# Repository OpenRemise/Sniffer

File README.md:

# Sniffer

<a href="https://openremise.at">
<picture>
  <source media="(prefers-color-scheme: dark)" srcset="https://github.com/OpenRemise/.github/raw/master/data/icons/icon_dark.svg">
  
</picture>
</a>

The Sniffer is a small add-on board that turns a [Raspberry Pi Pico](https://www.raspberrypi.com/products/raspberry-pi-pico) into a [DCC](https://en.wikipedia.org/wiki/Digital_Command_Control) (and BiDi) logic analyzer.

### Features
- **Requires** [Raspberry Pi Pico](https://www.raspberrypi.com/products/raspberry-pi-pico) (or [Pico 2](https://www.raspberrypi.com/products/raspberry-pi-pico-2))
- No external supply
- ≥12V track voltage
- 3.3V logic level outputs for
  - P track
  - N track
  - BiDi
  - BiDi polarity
- Opto-isolation
- Supported software
  - [PulseView](https://github.com/sigrokproject/pulseview)
  - [LogicAnalyzer](https://github.com/gusmanb/logicanalyzer)

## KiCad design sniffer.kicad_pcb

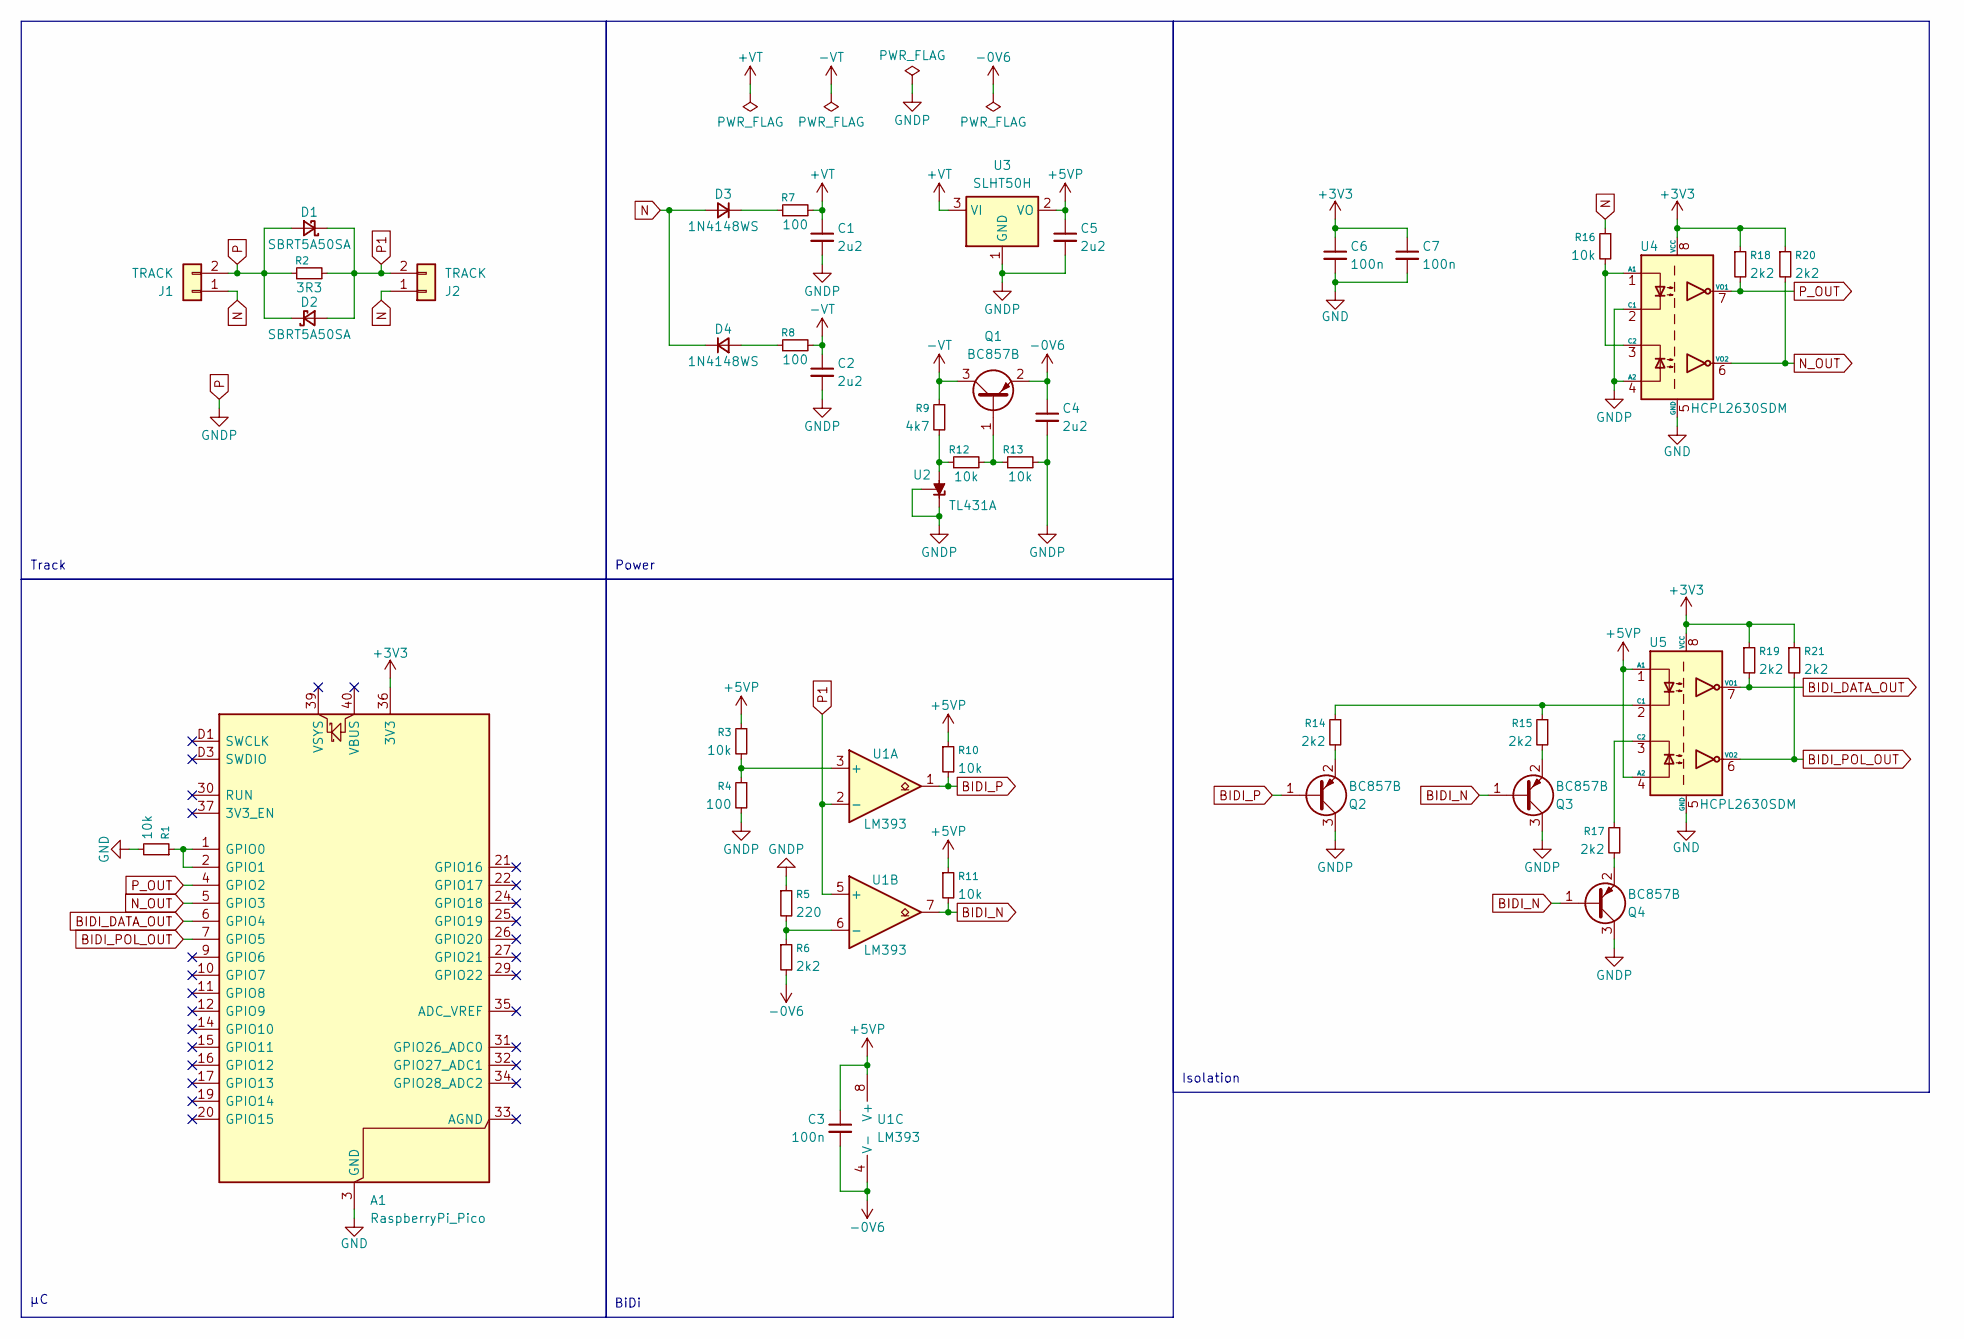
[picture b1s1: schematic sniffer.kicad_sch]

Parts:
A1: RaspberryPi_Pico; RaspberryPi_Pico_SMD_HandSolder
C1, C2, C4, C5: 2u2; C_1206_3216Metric_Pad1.33x1.80mm_HandSolder
C3, C6, C7: 100n; C_0805_2012Metric_Pad1.18x1.45mm_HandSolder
D1, D2: SBRT5A50SA; D_SMA_Handsoldering
D3, D4: 1N4148WS; D_SOD-323_HandSoldering
J1, J2: TRACK; PhoenixContact_MC_1,5_2-G-3.5_1x02_P3.50mm_Horizontal
Q1, Q2, Q3, Q4: BC857B; SOT-23_Handsoldering
R1, R3, R10, R11, R12, R13, R16: 10k; R_0805_2012Metric_Pad1.20x1.40mm_HandSolder
R2: 3R3; R_0805_2012Metric_Pad1.20x1.40mm_HandSolder
R4, R7, R8: 100; R_0805_2012Metric_Pad1.20x1.40mm_HandSolder
R5: 220; R_0805_2012Metric_Pad1.20x1.40mm_HandSolder
R6, R14, R15, R17, R18, R19, R20, R21: 2k2; R_0805_2012Metric_Pad1.20x1.40mm_HandSolder
R9: 4k7; R_0805_2012Metric_Pad1.20x1.40mm_HandSolder
U1: LM393; SOIC-8_3.9x4.9mm_P1.27mm
U2: TL431A; SOT-23_Handsoldering
U3: SLHT50H; SOT-23_Handsoldering
U4, U5: HCPL2630SDM; SMDIP-8_W9.53mm

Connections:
+3V3: A1.36 (3V3), C6.1, C7.1, R18.1, R19.1, R20.1, R21.1, U4.8 (VCC), U5.8 (VCC)
+5VP: C3.1, C5.1, R3.1, R10.1, R11.1, U1.8 (V+), U3.2 (VO), U5.1 (A1), U5.4 (A2)
+VT: C1.1, R7.2, U3.3 (VI)
-0V6: C3.2, C4.1, Q1.2 (E), R6.2, U1.4 (V-)
-VT: C2.1, Q1.3 (C), R8.2, R9.1
BIDI_DATA_OUT: A1.6 (GPIO4), R19.2, U5.7 (VO1)
BIDI_N: Q3.1 (B), Q4.1 (B), R11.2, U1.7
BIDI_P: Q2.1 (B), R10.2, U1.1
BIDI_POL_OUT: A1.7 (GPIO5), R21.2, U5.6 (VO2)
GND: A1.3 (GND), A1.8 (GND), A1.13 (GND), A1.18 (GND), A1.23 (GND), A1.28 (GND), A1.38 (GND), A1.D2 (GND), C6.2, C7.2, R1.2, U4.5 (GND), U5.5 (GND)
N: D3.2 (A), D4.1 (K), J1.1, J2.1, R16.1
N_OUT: A1.5 (GPIO3), R20.2, U4.6 (VO2)
unnamed: A1.1 (GPIO0), A1.2 (GPIO1), R1.1
unnamed: D3.1 (K), R7.1
unnamed: D4.2 (A), R8.1
unnamed: Q1.1 (B), R12.2, R13.1
unnamed: Q2.2 (E), R14.2
unnamed: Q3.2 (E), R15.2
unnamed: Q4.2 (E), R17.2
unnamed: R3.2, R4.1, U1.3 (+)
unnamed: R5.2, R6.1, U1.6 (-)
unnamed: R9.2, R12.1, U2.3 (A)
unnamed: R16.2, U4.1 (A1), U4.3 (C2)
unnamed: R14.1, R15.1, U5.2 (C1)
unnamed: R17.1, U5.3 (C2)
P: C1.2, C2.2, C4.2, C5.2, D1.2 (A), D2.1 (K), J1.2, Q2.3 (C), Q3.3 (C), Q4.3 (C), R2.1, R4.2, R5.1, R13.2, U2.1 (K), U2.2 (REF), U3.1 (GND), U4.2 (C1), U4.4 (A2)
P1: D1.1 (K), D2.2 (A), J2.2, R2.2, U1.2 (-), U1.5 (+)
P_OUT: A1.4 (GPIO2), R18.2, U4.7 (VO1)

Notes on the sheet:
BiDi
Isolation
Track
Power

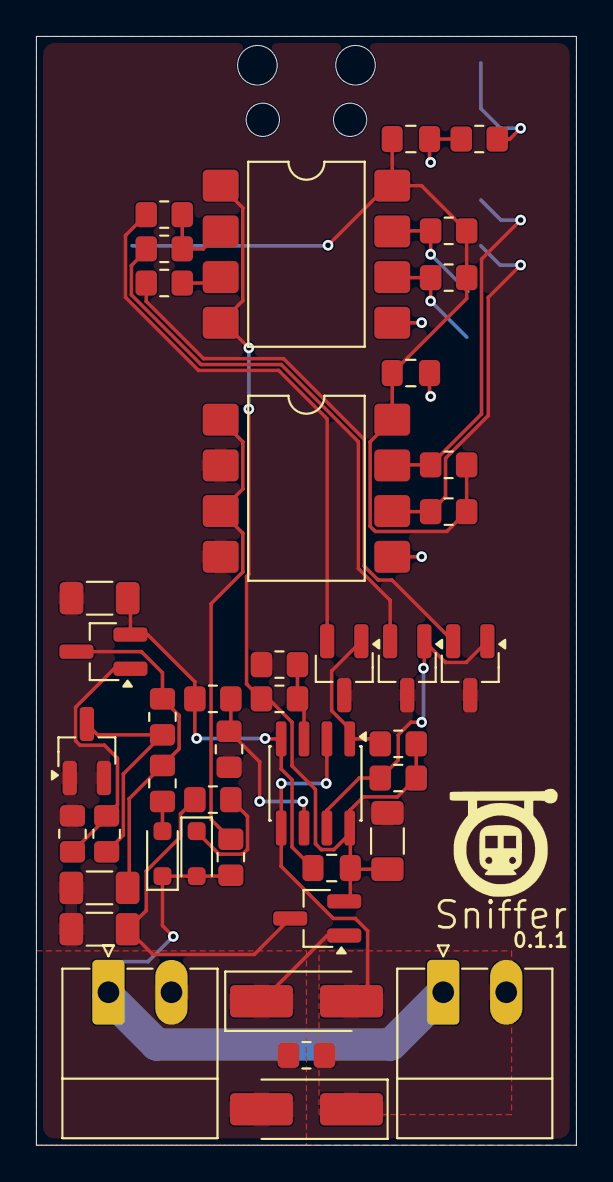
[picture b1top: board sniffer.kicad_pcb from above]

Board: 2 copper layers, 30.0 x 61.6 mm, 44 parts (1 on the bottom side), 28 nets.

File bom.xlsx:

|  |  | S3Main PCS BOM
Item # | *Designator | *Qty | Manufacturer | *Mfg Part # | Description / Value | *Package/Footprint | Type | Your Instructions / Notes
1 | A1 | 1 | Raspberry Pi | SC1631 | RASPBERRY PI PICO 2 RP2350 |  | SMD
2 | C1,C2,C4,C5 | 4 | Samsung Electro-Mechanics | CL31B225KBHNNNE | CAP CER 2.2UF 50V X7R 1206 | 1206 | SMD
3 | C3,C6,C7 | 3 | Samsung Electro-Mechanics | CL21B104KBCNNNC | CAP CER 0.1UF 50V X7R 0805 | 0805 | SMD
4 | D1,D2 | 2 | Diodes Incorporated | SBRT5A50SA-13 | DIODE SBR 50V 5A SMA | SMA | SMD
5 | D3,D4 | 2 | Diodes Incorporated | 1N4148WS-7-F | DIODE STANDARD 75V 150MA SOD323 | SOD-323 | SMD
6 | J1,J2 | 2 | Phoenix Contact | 1844210 | TERM BLOCK HDR 2POS 90DEG 3.5MM |  | THT
7 | Q1,Q2,Q3,Q4 | 4 | Taiwan Semiconductor Corporation | BC857A RFG | TRANS PNP 45V 0.1A SOT-23 | SOT-23-3 | SMD
8 | R1,R3,R10,R11,R12,R13,R16 | 7 | YAGEO | RC0805FR-0710KL | RES 10K OHM 1% 1/8W 0805 | 0805 | SMD
9 | R2 | 1 | Vishay Dale | RCS08053R30FKEA | RES 3.3 OHM 1% 3/4W 0805 | 0805 | SMD
10 | R4,R7,R8 | 3 | YAGEO | RC0805FR-07100RL | RES 100 OHM 1% 1/8W 0805 | 0805 | SMD
11 | R5 | 1 | YAGEO | RC0805FR-07220RL | RES 220 OHM 1% 1/8W 0805 | 0805 | SMD
12 | R6,R14,R15,R17,R18,R19,R20,R21 | 8 | YAGEO | RC0805FR-072K2L | RES 2.2K OHM 1% 1/8W 0805 | 0805 | SMD
13 | R9 | 1 | YAGEO | RC0805FR-074K7L | RES 4.7K OHM 1% 1/8W 0805 | 0805 | SMD
14 | U1 | 1 | onsemi | LM393DR2G | IC COMPARATOR 2 GEN PUR 8SOIC | SOIC-8 | SMD
15 | U2 | 1 | EVVO | TL431A | V-REF ADJUSTABLE 2.5V TO 36V 100 | SOT-23-3 | SMD
16 | U3 | 1 | Shenzhen Slkormicro Semicon Co., Ltd. | SLHT50H | 250MA FIXED 5V POSITIVE 50V SOT- | SOT-23-3 | SMD | Alternatively AP7375-50SR-7
17 | U4,U5 | 2 | onsemi | HCPL2630SDM | OPTOISO 5KV 2CH OPEN COLL 8-SMD | SMD-8 | SMD

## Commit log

2026-06-05 feat: revision 0.1.0
2026-06-22 docs: add documentation
2026-06-23 fix: U3 regulator pins flipped (#1)
2026-06-24 chore: suitable names for `BIDI_DATA` and `BIDI_POL`
